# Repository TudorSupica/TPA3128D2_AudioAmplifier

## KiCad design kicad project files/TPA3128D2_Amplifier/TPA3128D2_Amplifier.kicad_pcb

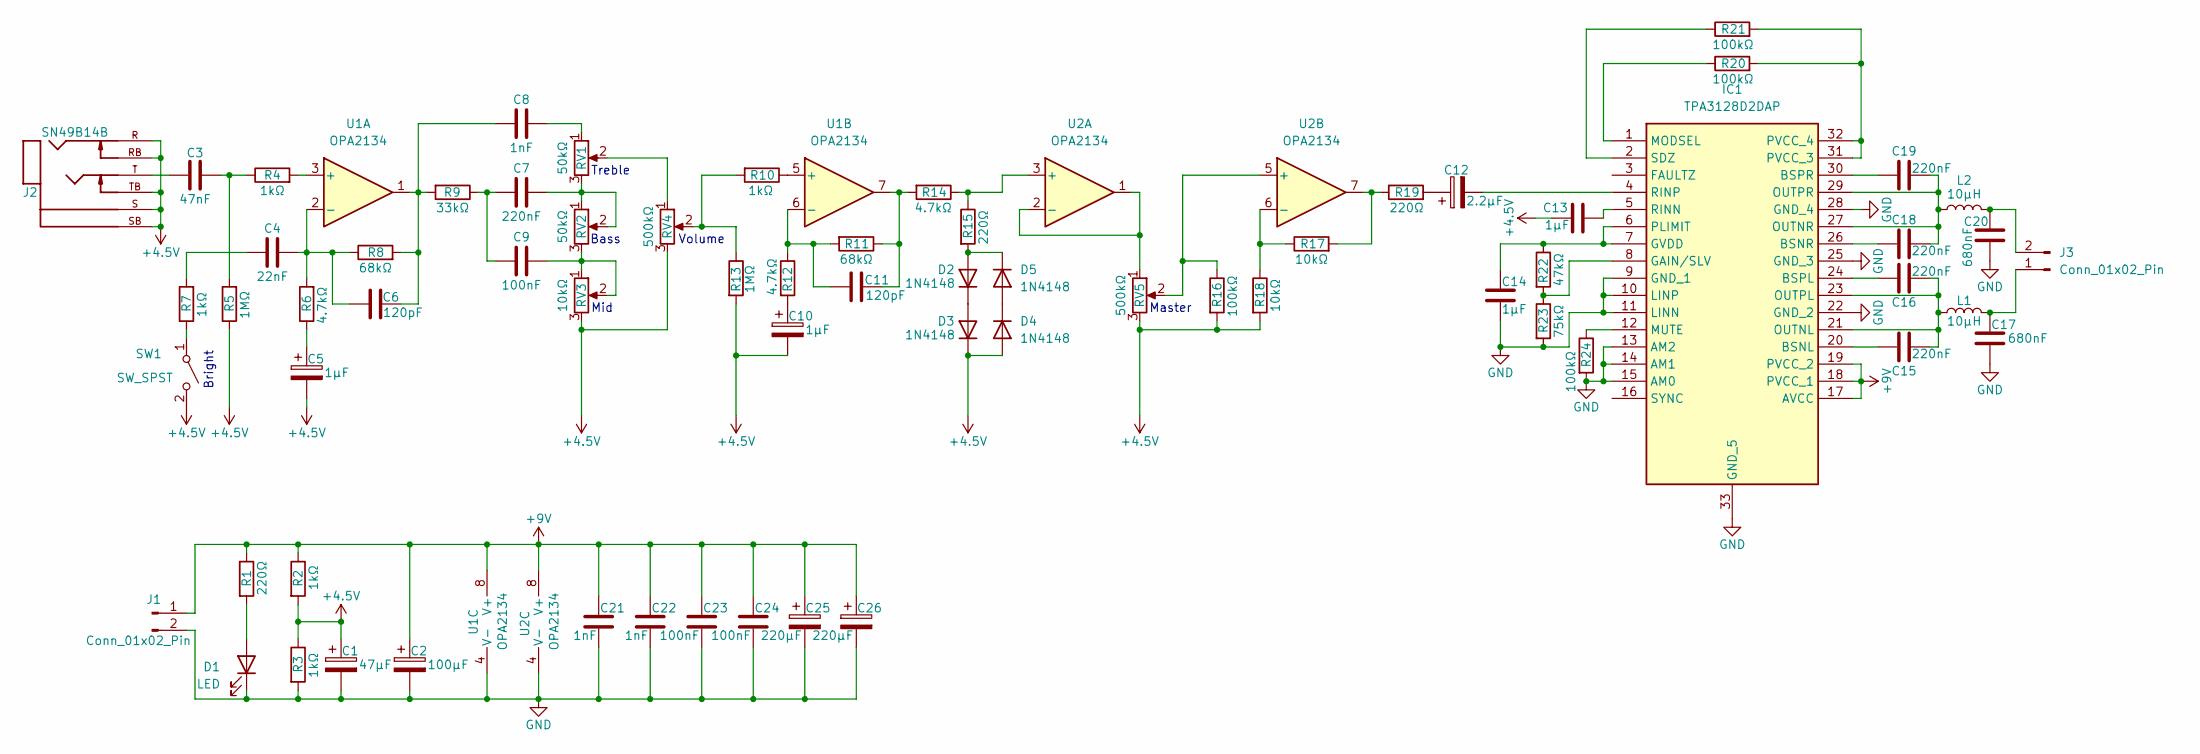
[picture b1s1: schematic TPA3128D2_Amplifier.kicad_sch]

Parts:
C1: 47µF; CP_Radial_D5.0mm_P2.00mm
C2: 100µF; CP_Radial_D5.0mm_P2.00mm
C3: 47nF; C_Rect_L4.6mm_W3.0mm_P2.50mm_MKS02_FKP02
C4: 22nF; C_Rect_L4.6mm_W3.0mm_P2.50mm_MKS02_FKP02
C5, C10: 1µF; CP_Radial_D5.0mm_P2.00mm
C6, C11: 120pF; C_Rect_L4.6mm_W3.0mm_P2.50mm_MKS02_FKP02
C7, C15, C16, C18, C19: 220nF; C_Rect_L4.6mm_W3.0mm_P2.50mm_MKS02_FKP02
C8, C21, C22: 1nF; C_Rect_L4.6mm_W3.0mm_P2.50mm_MKS02_FKP02
C9, C23, C24: 100nF; C_Rect_L4.6mm_W3.0mm_P2.50mm_MKS02_FKP02
C12: 2.2µF; CP_Radial_D5.0mm_P2.00mm
C13, C14: 1µF; C_Rect_L4.6mm_W3.0mm_P2.50mm_MKS02_FKP02
C17, C20: 680nF; C_Rect_L4.6mm_W3.0mm_P2.50mm_MKS02_FKP02
C25, C26: 220µF; CP_Radial_D5.0mm_P2.00mm
D1: LED; LED_D5.0mm_Clear
D2, D3, D4, D5: 1N4148; D_DO-35_SOD27_P7.62mm_Horizontal
IC1: TPA3128D2DAP; SOP65P810X120-33N; Manufacturer_Part_Number TPA3128D2DAP; Mouser Part Number 595-TPA3128D2DAP
J1: Conn_01x02_Pin; PinHeader_1x02_P2.00mm_Vertical
J2: SN49B14B; PJ-644C; PARTREV F
J3: Conn_01x02_Pin; JWT_A3963_1x02_P3.96mm_Vertical
L1, L2: 10µH; L_Axial_L6.6mm_D2.7mm_P10.16mm_Horizontal_Vishay_IM-2
R1, R15, R19: 220Ω; R_Axial_DIN0207_L6.3mm_D2.5mm_P7.62mm_Horizontal
R2, R3, R4, R7, R10: 1kΩ; R_Axial_DIN0207_L6.3mm_D2.5mm_P7.62mm_Horizontal
R5, R13: 1MΩ; R_Axial_DIN0207_L6.3mm_D2.5mm_P7.62mm_Horizontal
R6, R12, R14: 4.7kΩ; R_Axial_DIN0207_L6.3mm_D2.5mm_P7.62mm_Horizontal
R8, R11: 68kΩ; R_Axial_DIN0207_L6.3mm_D2.5mm_P7.62mm_Horizontal
R9: 33kΩ; R_Axial_DIN0207_L6.3mm_D2.5mm_P7.62mm_Horizontal
R16, R20, R21, R24: 100kΩ; R_Axial_DIN0207_L6.3mm_D2.5mm_P7.62mm_Horizontal
R17, R18: 10kΩ; R_Axial_DIN0207_L6.3mm_D2.5mm_P7.62mm_Horizontal
R22: 47kΩ; R_Axial_DIN0207_L6.3mm_D2.5mm_P7.62mm_Horizontal
R23: 75kΩ; R_Axial_DIN0207_L6.3mm_D2.5mm_P7.62mm_Horizontal
RV1, RV2: 50kΩ; Potentiometer_Alpha_RD901F-40-00D_Single_Vertical
RV3: 10kΩ; Potentiometer_Alpha_RD901F-40-00D_Single_Vertical
RV4, RV5: 500kΩ; Potentiometer_Alpha_RD901F-40-00D_Single_Vertical
SW1: SW_SPST; PinHeader_1x02_P2.00mm_Vertical
U1, U2: OPA2134; DIP-8_W7.62mm

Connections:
+4.5V: C1.1, C5.2, C10.2, C13.1, D3.1 (K), D4.2 (A), J2.R, J2.RB, J2.S, J2.SB, J2.TB, R2.2, R3.1, R5.1, R13.2, R16.2, R18.2, RV3.3, RV4.3, RV5.3, SW1.2 (B)
+9V: C2.1, C21.1, C22.1, C23.1, C24.1, C25.1, C26.1, IC1.17 (AVCC), IC1.18 (PVCC_1), IC1.19 (PVCC_2), J1.1, R1.1, R2.1, U1.8 (V+), U2.8 (V+)
GND: C1.2, C2.2, C14.1, C17.2, C20.2, C21.2, C22.2, C23.2, C24.2, C25.2, C26.2, D1.1 (K), IC1.9 (GND_1), IC1.10 (LINP), IC1.11 (LINN), IC1.13 (AM2), IC1.14 (AM1), IC1.15 (AM0), IC1.22 (GND_2), IC1.25 (GND_3), IC1.28 (GND_4), IC1.33 (GND_5), J1.2, R3.2, R23.2, R24.2, U1.4 (V-), U2.4 (V-)
unnamed: C3.1, J2.T
unnamed: C3.2, R4.1, R5.2
unnamed: C4.1, R7.2
unnamed: C5.1, R6.1
unnamed: C6.2, C8.1, R8.2, R9.2, U1.1
unnamed: C7.1, C9.1, R9.1
unnamed: C7.2, RV1.3, RV2.1, RV2.2
unnamed: C8.2, RV1.1
unnamed: C9.2, RV2.3, RV3.1, RV3.2
unnamed: C10.1, R12.2
unnamed: C11.2, R11.1, R14.2, U1.7
unnamed: C12.1, R19.2
unnamed: D1.2 (A), R1.2
unnamed: D2.2 (A), D5.1 (K), R15.2
unnamed: D2.1 (K), D3.2 (A)
unnamed: D4.1 (K), D5.2 (A)
unnamed: C15.2, IC1.20 (BSNL)
unnamed: C18.2, IC1.26 (BSNR)
unnamed: C16.2, IC1.24 (BSPL)
unnamed: C19.2, IC1.30 (BSPR)
unnamed: IC1.8 (GAIN/SLV), R22.2, R23.1
unnamed: C14.2, IC1.6 (PLIMIT), IC1.7 (GVDD), R22.1
unnamed: IC1.1 (MODSEL), R20.1
unnamed: IC1.12 (MUTE), R24.1
unnamed: C15.1, C16.1, IC1.21 (OUTNL), IC1.23 (OUTPL), L1.1
unnamed: C18.1, C19.1, IC1.27 (OUTNR), IC1.29 (OUTPR), L2.1
unnamed: IC1.31 (PVCC_3), IC1.32 (PVCC_4), R20.2, R21.2
unnamed: C13.2, IC1.5 (RINN)
unnamed: C12.2, IC1.4 (RINP)
unnamed: IC1.2 (SDZ), R21.1
unnamed: C17.1, J3.1, L1.2
unnamed: C20.1, J3.2, L2.2
unnamed: R10.2, R13.1, RV4.2
unnamed: R17.2, R19.1, U2.7
unnamed: RV1.2, RV4.1
unnamed: R7.1, SW1.1 (A)
unnamed: R4.2, U1.3 (+)
unnamed: C4.2, C6.1, R6.2, R8.1, U1.2 (-)
unnamed: R10.1, U1.5 (+)
unnamed: C11.1, R11.2, R12.1, U1.6 (-)
unnamed: R14.1, R15.1, U2.3 (+)
unnamed: RV5.1, U2.1, U2.2 (-)
unnamed: R16.1, RV5.2, U2.5 (+)
unnamed: R17.1, R18.1, U2.6 (-)

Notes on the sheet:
Bright
Bass
Treble
Mid
Master
Volume

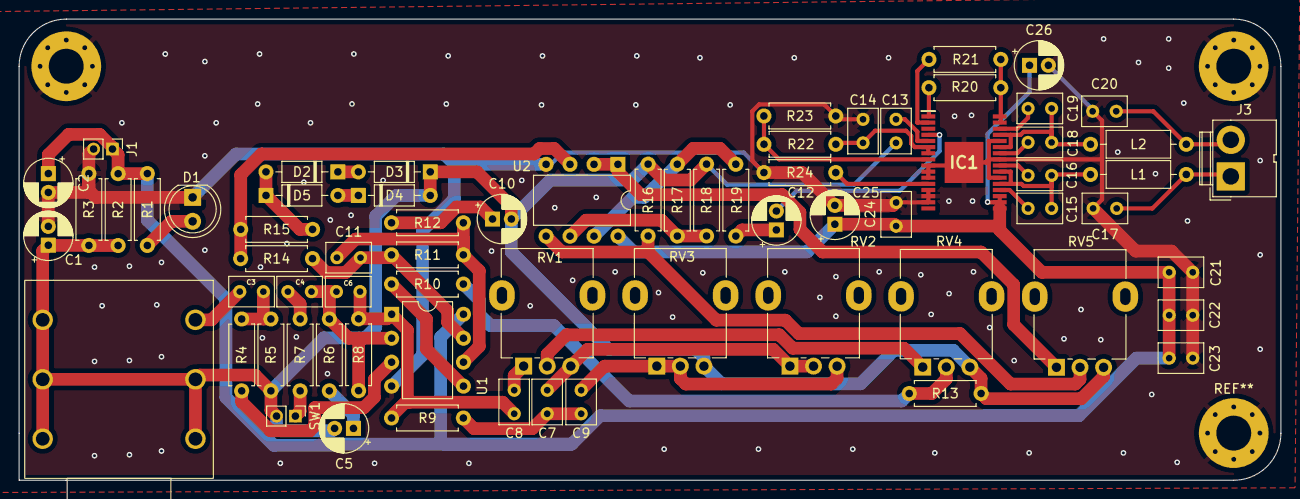
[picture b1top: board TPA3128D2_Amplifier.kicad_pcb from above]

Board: 2 copper layers, 133.8 x 48.9 mm, 69 parts (0 on the bottom side), 47 nets.

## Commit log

2024-08-01 Added schematic and PCB
